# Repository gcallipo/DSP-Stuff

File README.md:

# DSP stuff
This project define a space on which to share components, algorithms and exercises concerning 
the world of digital signal analysis, this includes SDR techniques, Audio and Video manipulation, 
controls etc.

**Included Projects:**

#### Audio Filter Convolutional F32:	
	
	This is a specific audio signal filtering technique implemented 
	in the frequency domain.
	
	This software is based on the  AudioFilterConvolution routine 
	Written by Brian Millier on Mar 2017, more infos here:
	https://circuitcellar.com/research-design-hub/fancy-filtering-with-the-teensy-3-6/
	
	and modified by Giuseppe Callipo-ik8yfw (myself)
	
	Modification:
	
		* Class refactoring, change some methods visibility;
		* Filter coefficients calculation included into class;
		* Change the class for running in both with F32  OpenAudio_ArduinoLibrary for Teensy;	
		* Added initFilter method for single anf fast initialization and on the fly reinititializzation; 
		* Optimize it to use as output audio filter on SDR receiver.
		* Optimize execution time

#### Audio DSP Filter Chain:	
		
	This is an audio signal filtering combo that included
	various operation in a single block.
	The block works at the sample rate of 44.1kHz and apply 
	a decimation factor by 4, then the real audio bandwidth is 
	about 5kHz suitable for SSB and AM station.
	
	It allow to execute the following operations:
	
	* Spectral Subtraction for Noise Reduction, it works well on ShorthWave Receiver  ( OPERATIVE )
	* BPF Filtering as band pass filtering        ( OPERATIVE )
	* LMS Noise Reduction as alternative technic  ( TO BE ADDED )
	* and more others will be added 
		
	**NOTE**: credits are added into the source files.
	** This is still work in progress and can be changed. ** 
	
Tests on receiver RadioDSP Sdr:

       Spectral subtractio  https://youtu.be/6Mxtmje6WIE
       
 #### HF PRE Selector schematic:	
		
	This is a schematic written on Kicad free software
	to build a good HF filter reception frontend for 
	any Short Wave Radio Receiver. Inside the project
	you can find also a PDF version of schematic.
	I use two cheap multiplexer modules and some passive
	components to define each filter band. 
	It was successfully tested with the Radio DSP SDR Receiver

#### NOTE:

All software and hw schematics included in the projects are intended as opensources.
(Updated on 08.08.2022)

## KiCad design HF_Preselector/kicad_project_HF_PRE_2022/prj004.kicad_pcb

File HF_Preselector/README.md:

#### HF PRE Selector schematic:	
		
	This is a schematic written on Kicad free software
	to build a good HF filter reception frontend for 
	any Short Wave Radio Receiver. Inside the project
	you can find also a PDF version of schematic.
	I use two cheap multiplexer modules and some passive
	components to define each filter band. 
	It was successfully tested with the Radio DSP SDR Receiver.

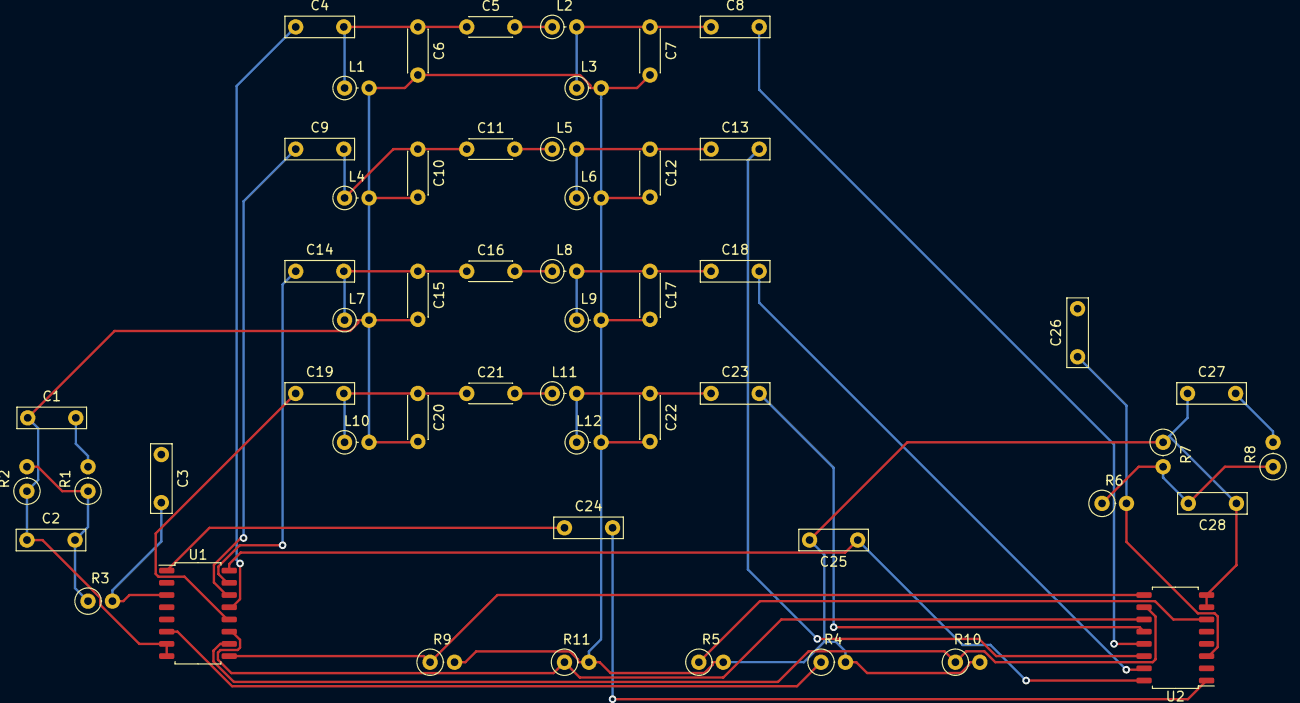
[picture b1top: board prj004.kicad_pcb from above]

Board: 2 copper layers, 53 parts (0 on the bottom side), 35 nets.

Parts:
C1, C2, C3, C4, C8, C9, C13, C14, C18, C19, C23, C24, C25, C26, C27, C28: 100n; C_Rect_L7.0mm_W2.0mm_P5.00mm
C5: 680; C_Disc_D4.3mm_W1.9mm_P5.00mm
C6, C7: 1500; C_Disc_D4.3mm_W1.9mm_P5.00mm
C10, C12: 820; C_Disc_D4.3mm_W1.9mm_P5.00mm
C11, C15, C17: 390; C_Disc_D4.3mm_W1.9mm_P5.00mm
C16, C20, C22: 180; C_Disc_D4.3mm_W1.9mm_P5.00mm
C21: 82; C_Disc_D4.3mm_W1.9mm_P5.00mm
L1, L3, L5: 2.2uH; L_Axial_L5.3mm_D2.2mm_P2.54mm_Vertical_Vishay_IM-1
L2: 4.7uH; L_Axial_L5.3mm_D2.2mm_P2.54mm_Vertical_Vishay_IM-1
L4, L6, L8: 1uH; L_Axial_L5.3mm_D2.2mm_P2.54mm_Vertical_Vishay_IM-1
L7, L9: 0.47uH; L_Axial_L5.3mm_D2.2mm_P2.54mm_Vertical_Vishay_IM-1
L10, L12: 0.33uH; L_Axial_L5.3mm_D2.2mm_P2.54mm_Vertical_Vishay_IM-1
L11: 0.68uH; L_Axial_L5.3mm_D2.2mm_P2.54mm_Vertical_Vishay_IM-1
R1, R2, R7, R8: 15k; R_Axial_DIN0207_L6.3mm_D2.5mm_P2.54mm_Vertical
R3, R6: 10k; R_Axial_DIN0207_L6.3mm_D2.5mm_P2.54mm_Vertical
R4, R5, R9, R10, R11: 1k; R_Axial_DIN0207_L6.3mm_D2.5mm_P2.54mm_Vertical
U1, U2: 74HC4051; SOP-16_4.55x10.3mm_P1.27mm

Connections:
+5V: C25.1, U1.16, U2.16
GNDREF: C1.1, C2.1, C6.2, C7.2, C10.2, C12.2, C15.2, C17.2, C20.2, C22.2, C25.2, C27.1, C28.1, L1.2, L3.2, L4.2, L6.2, L7.2, L9.2, L10.2, L12.2, R2.1, R4.2, R5.2, R7.1, R9.2, R10.2, R11.2, U1.7, U1.8, U2.7, U2.8
unnamed: C1.2, R1.2
unnamed: C2.2, R1.1, R2.2, R3.1
unnamed: C3.2, R3.2, U1.3
unnamed: C4.1, U1.13
unnamed: C4.2, C5.1, C6.1, L1.1
unnamed: C5.2, L2.1
unnamed: C7.1, C8.1, L2.2, L3.1
unnamed: C8.2, U2.13
unnamed: C9.1, U1.14
unnamed: C9.2, C10.1, C11.1, L4.1
unnamed: C11.2, L5.1
unnamed: C12.1, C13.1, L5.2, L6.1
unnamed: C13.2, U2.14
unnamed: C14.1, U1.15
unnamed: C14.2, C15.1, C16.1, L7.1
unnamed: C16.2, L8.1
unnamed: C17.1, C18.1, L8.2, L9.1
unnamed: C18.2, U2.15
unnamed: C19.1, U1.12
unnamed: C19.2, C20.1, C21.1, L10.1
unnamed: C21.2, L11.1
unnamed: C22.1, C23.1, L11.2, L12.1
unnamed: C23.2, U2.12
unnamed: C24.1, U1.1
unnamed: C24.2, U2.1
unnamed: C26.1, R6.2, U2.3
unnamed: C27.2, R8.2
unnamed: C28.2, R6.1, R7.2, R8.1
unnamed: R4.1, U1.6
unnamed: R5.1, U2.6
S0: R11.1, U1.11, U2.11
S1: R10.1, U1.10, U2.10
S2: R9.1, U1.9, U2.9

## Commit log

2021-05-02 Initial commit
    Initial Comming and first subproject creation
2022-01-29 Add DSP chanin block
2022-01-29 added fir functions
2022-01-30 Moda on readme
2022-01-30 Update on readme
2022-02-05 Added BPF Filter
    Added BPF Filter into decimated slow path
2022-02-05 update description
2022-02-06 Experimental Version
    Experimental version with time execution optimization ( the time for update change from 248 uSec to 139 uSec )
2022-02-08 Update time optimization
    Optimized versione in time and space.
    version 2.0.0
2022-08-08 Update README.md
    Add new section : HF Pre Selector Schematic
2022-08-08 Add files via upload
    Committed new hf pre selector project
2022-08-08 Create README.md
    Add subsection readme
2022-08-08 Add files via upload
    BOM in html format
2022-08-08 Add files via upload
    Add Bill of material in txt format
2022-08-09 Delete HF_PRE_schematic.pdf
    deleted for upgrade
2022-08-09 Delete HF_Preselector/kicad_project_HF_PRE_2022 directory
    deleted for change
2022-08-09 Add files via upload
    Add new files
2022-11-10 Correction on schematic
    ERRATE CORRIGE: corrected an error in schematic near the contravers connection.
